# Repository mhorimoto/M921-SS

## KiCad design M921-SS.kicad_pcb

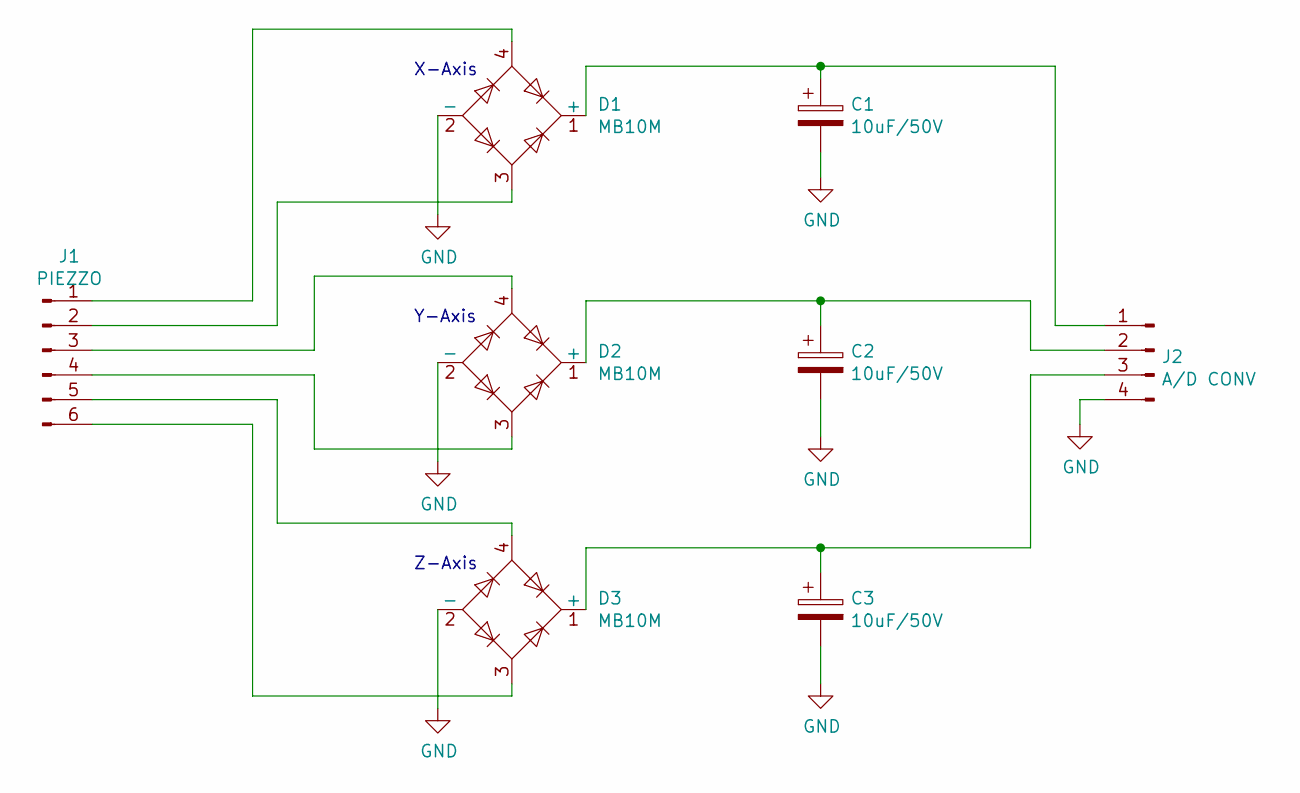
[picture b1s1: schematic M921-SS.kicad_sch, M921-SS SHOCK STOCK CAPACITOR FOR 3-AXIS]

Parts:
C1, C2, C3: 10uF/50V; CP_Radial_D5.0mm_P2.00mm
D1, D2, D3: MB10M
J1: PIEZZO; JST_XH_B6B-XH-A_1x06_P2.50mm_Vertical
J2: A/D CONV; JST_XH_B4B-XH-A_1x04_P2.50mm_Vertical

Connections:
GND: C1.2, C2.2, C3.2, D1.2 (-), D2.2 (-), D3.2 (-), J2.4
unnamed: C1.1, D1.1 (+), J2.1
unnamed: C2.1, D2.1 (+), J2.2
unnamed: C3.1, D3.1 (+), J2.3
unnamed: D1.3, J1.2
unnamed: D1.4, J1.1
unnamed: D2.3, J1.4
unnamed: D2.4, J1.3
unnamed: D3.3, J1.6
unnamed: D3.4, J1.5

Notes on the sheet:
Z-Axis
Y-Axis
X-Axis

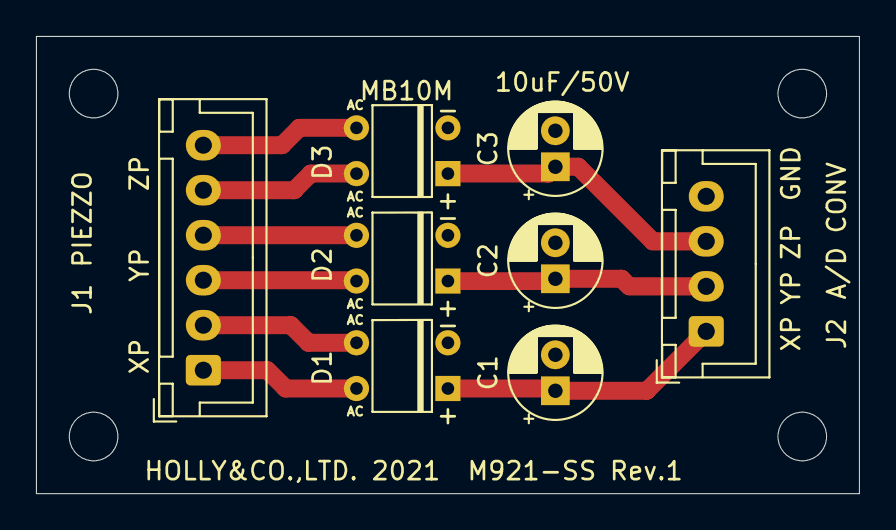
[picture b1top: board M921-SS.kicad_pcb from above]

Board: 2 copper layers, 45.7 x 25.4 mm, 8 parts (0 on the bottom side), 10 nets.

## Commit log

2021-09-19 Rev.1 PCBGOGO ordering data
2022-06-28 KiCAD New version
2022-06-28 KiCAD version up
2022-12-10 Piezzo holder by 3D printer
2023-02-13 sche: KiCAD new version
2024-06-21 KiCAD v8
